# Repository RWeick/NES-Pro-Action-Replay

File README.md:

# NES-Pro-Action-Replay
Everything necessary to produce the Pro Action Replay for the NES. Happy making.

The PAL's logic decodes to:

/SRAM.CS1.OE = ROMSEL.Sys and Addr: 0x5000 - 0x5FFF

/CPU_FF_CLK = /ROMSEL.Sys and PPU_EN and Addr: 0x7FFA

/PPU_FF_CLK = /ROMSEL.Sys and Addr: 0x7FF8

PCB Thickness: 1.6 mm

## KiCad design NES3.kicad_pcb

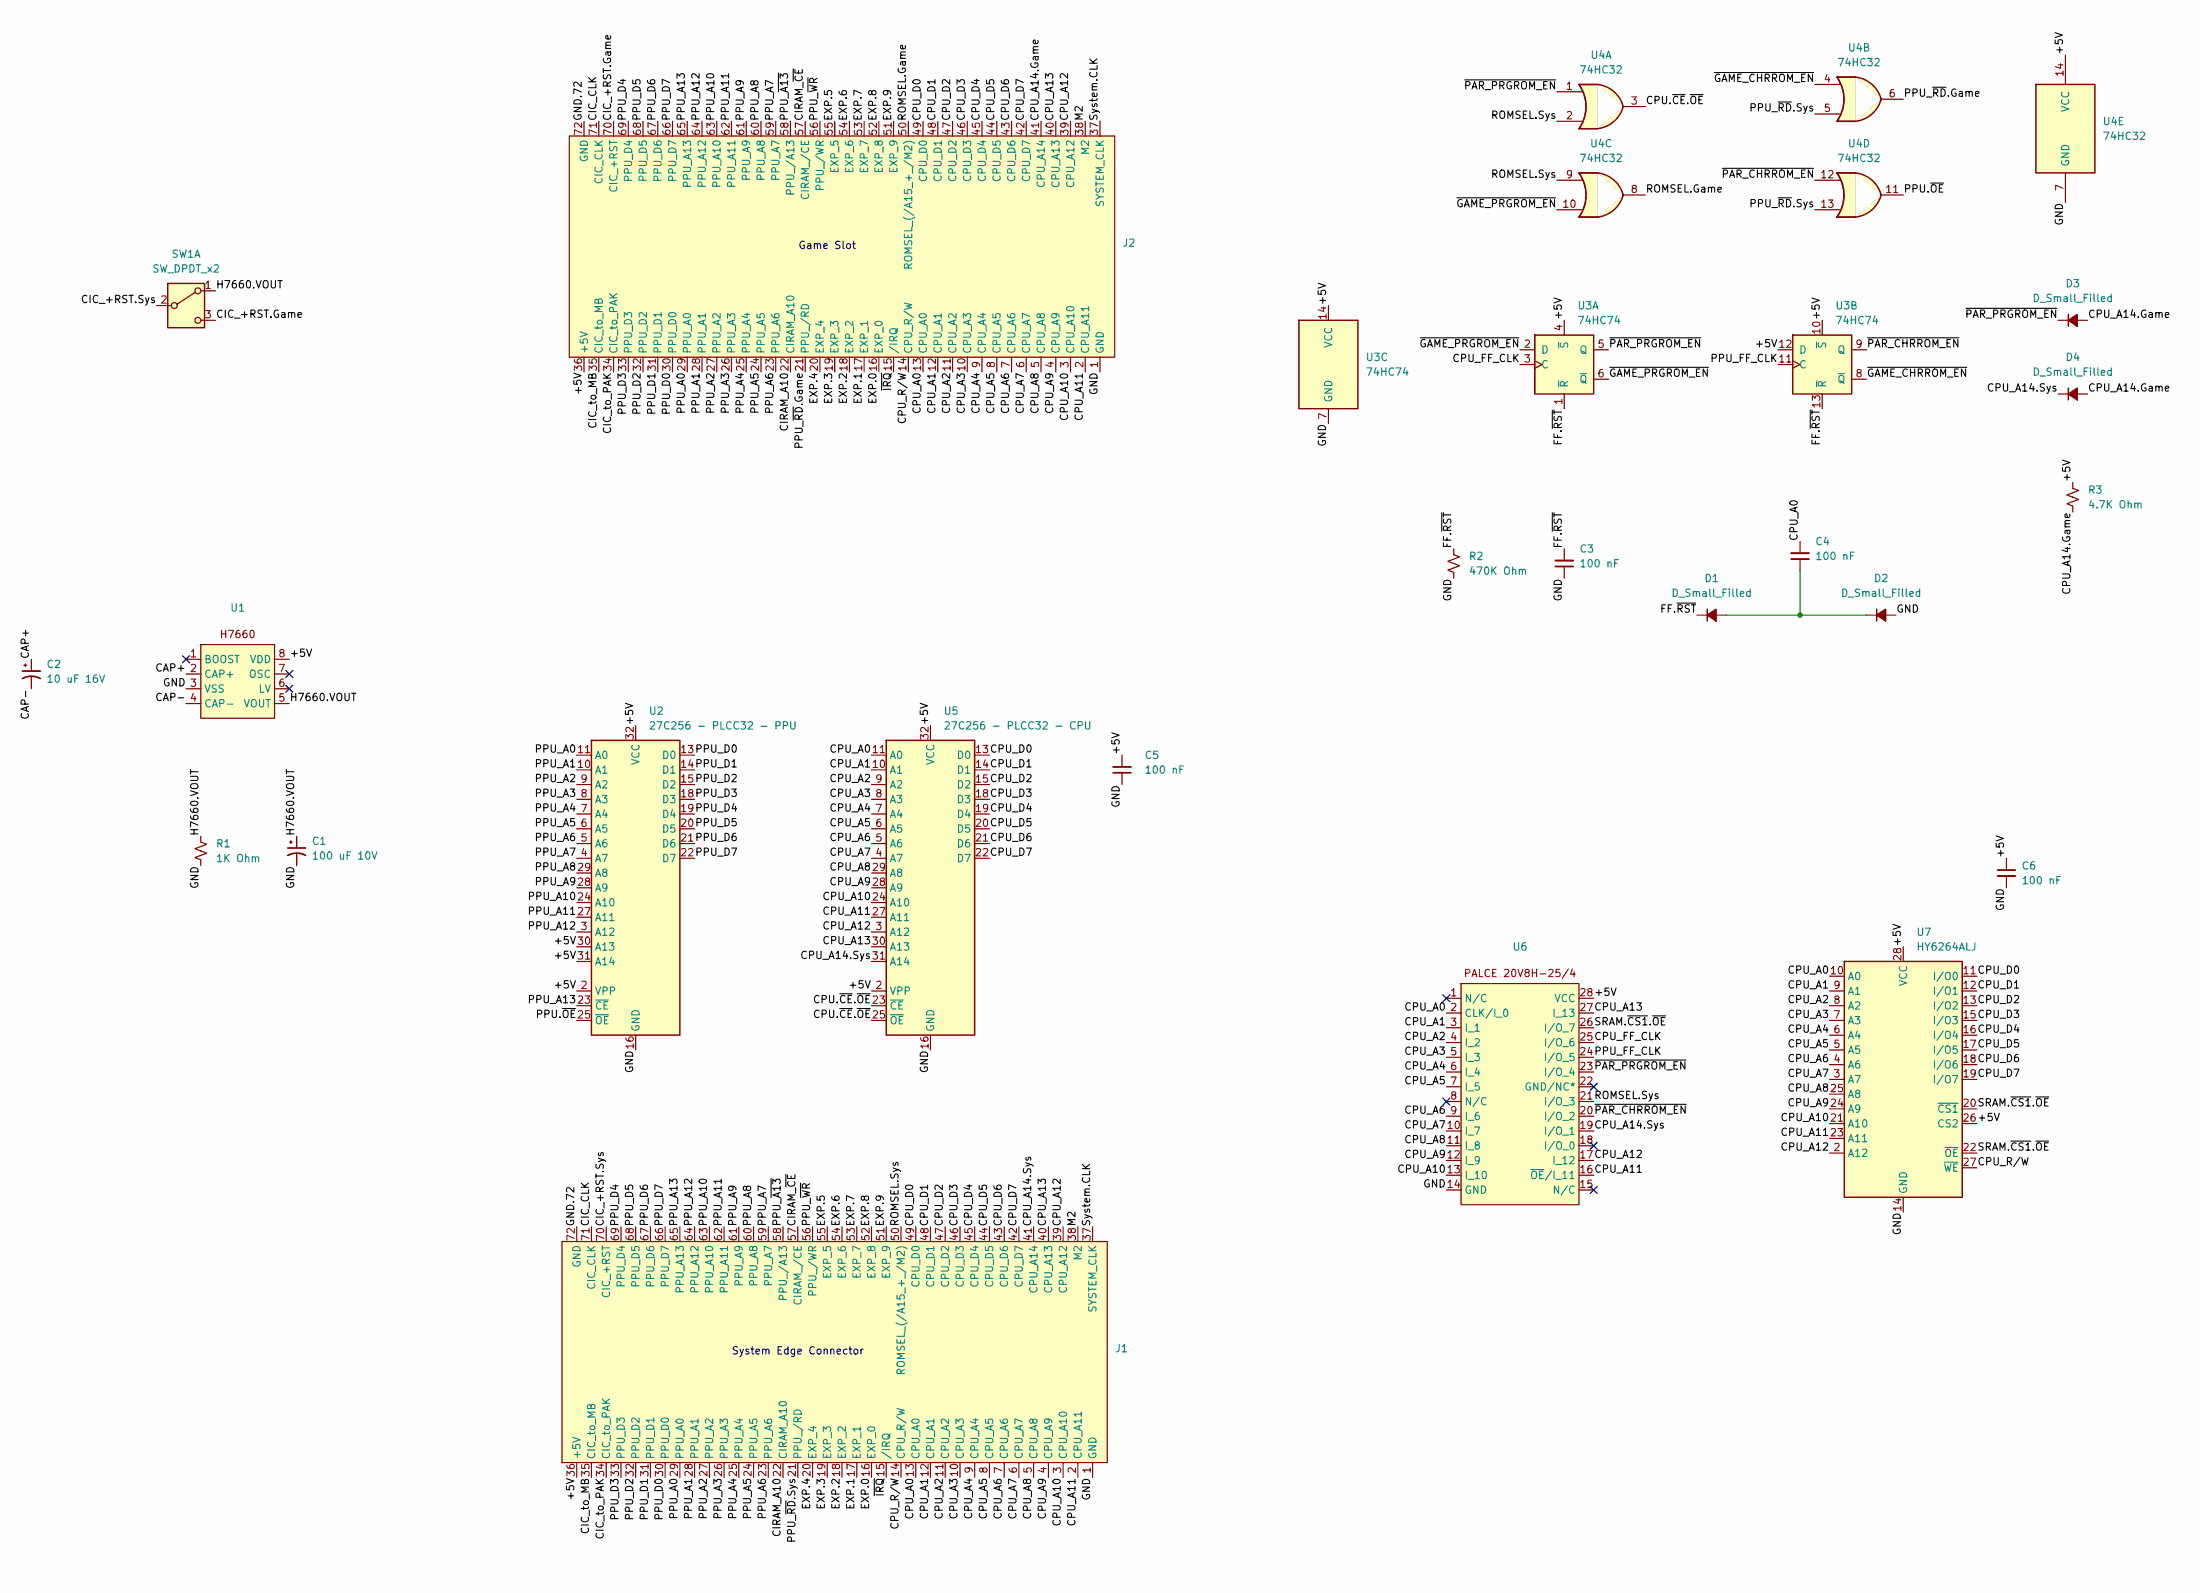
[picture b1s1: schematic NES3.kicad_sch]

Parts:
C1: 100 uF 10V; THT Caps
C2: 10 uF 16V; THT Caps
C3, C4, C5, C6: 100 nF; SMD Passive
D1, D2, D3, D4: D_Small_Filled; SMD Passive
J1: System Edge Connector
J2: Game Cartridge Slot
R1: 1K Ohm; SMD Passive
R2: 470K Ohm; SMD Passive
R3: 4.7K Ohm; SMD Passive
SW1: SW_DPDT_x2; Switch
U1: SOP-8
U2: 27C256 - PLCC32 - PPU; 27C256
U3: 74HC74; SOP-14
U4: 74HC32; SOP-14
U5: 27C256 - PLCC32 - CPU; 27C256
U6: PLCC-28
U7: HY6264ALJ; SRAM

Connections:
/+5V: C5.2, C6.1, J1.36 (+5V), J2.36 (+5V), R3.1, U1.8 (VDD), U2.2 (VPP), U2.30 (A13), U2.31 (A14), U2.32 (VCC), U3.4 (~S), U3.10 (~S), U3.12 (D), U3.14 (VCC), U4.14 (VCC), U5.2 (VPP), U5.32 (VCC), U6.28 (VCC), U7.26 (CS2), U7.28 (VCC)
/CAP+: C2.1, U1.2 (CAP+)
/CAP-: C2.2, U1.4 (CAP-)
/CIC_+RST.Game: J2.70 (CIC_+RST), SW1.3 (C)
/CIC_+RST.Sys: J1.70 (CIC_+RST), SW1.2 (B)
/CIC_CLK: J1.71 (CIC_CLK), J2.71 (CIC_CLK)
/CIC_to_MB: J1.35 (CIC_to_MB), J2.35 (CIC_to_MB)
/CIC_to_PAK: J1.34 (CIC_to_PAK), J2.34 (CIC_to_PAK)
/CIRAM_A10: J1.22 (CIRAM_A10), J2.22 (CIRAM_A10)
/CIRAM_~CE: J1.57 (CIRAM_/CE), J2.57 (CIRAM_/CE)
/CPU.~CE.~OE: U4.3, U5.23 (~CE), U5.25 (~OE)
/CPU_A0: C4.2, J1.13 (CPU_A0), J2.13 (CPU_A0), U5.11 (A0), U6.2 (CLK/I_0), U7.10 (A0)
/CPU_A1: J1.12 (CPU_A1), J2.12 (CPU_A1), U5.10 (A1), U6.3 (I_1), U7.9 (A1)
/CPU_A2: J1.11 (CPU_A2), J2.11 (CPU_A2), U5.9 (A2), U6.4 (I_2), U7.8 (A2)
/CPU_A3: J1.10 (CPU_A3), J2.10 (CPU_A3), U5.8 (A3), U6.5 (I_3), U7.7 (A3)
/CPU_A4: J1.9 (CPU_A4), J2.9 (CPU_A4), U5.7 (A4), U6.6 (I_4), U7.6 (A4)
/CPU_A5: J1.8 (CPU_A5), J2.8 (CPU_A5), U5.6 (A5), U6.7 (I_5), U7.5 (A5)
/CPU_A6: J1.7 (CPU_A6), J2.7 (CPU_A6), U5.5 (A6), U6.9 (I_6), U7.4 (A6)
/CPU_A7: J1.6 (CPU_A7), J2.6 (CPU_A7), U5.4 (A7), U6.10 (I_7), U7.3 (A7)
/CPU_A8: J1.5 (CPU_A8), J2.5 (CPU_A8), U5.29 (A8), U6.11 (I_8), U7.25 (A8)
/CPU_A9: J1.4 (CPU_A9), J2.4 (CPU_A9), U5.28 (A9), U6.12 (I_9), U7.24 (A9)
/CPU_A10: J1.3 (CPU_A10), J2.3 (CPU_A10), U5.24 (A10), U6.13 (I_10), U7.21 (A10)
/CPU_A11: J1.2 (CPU_A11), J2.2 (CPU_A11), U5.27 (A11), U6.16 (~OE/I_11), U7.23 (A11)
/CPU_A12: J1.39 (CPU_A12), J2.39 (CPU_A12), U5.3 (A12), U6.17 (I_12), U7.2 (A12)
/CPU_A13: J1.40 (CPU_A13), J2.40 (CPU_A13), U5.30 (A13), U6.27 (I_13)
/CPU_A14.Game: D3.2 (A), D4.2 (A), J2.41 (CPU_A14), R3.2
/CPU_A14.Sys: D4.1 (K), J1.41 (CPU_A14), U5.31 (A14), U6.19 (I/O_1)
/CPU_D0: J1.49 (CPU_D0), J2.49 (CPU_D0), U5.13 (D0), U7.11 (I/O0)
/CPU_D1: J1.48 (CPU_D1), J2.48 (CPU_D1), U5.14 (D1), U7.12 (I/O1)
/CPU_D2: J1.47 (CPU_D2), J2.47 (CPU_D2), U5.15 (D2), U7.13 (I/O2)
/CPU_D3: J1.46 (CPU_D3), J2.46 (CPU_D3), U5.18 (D3), U7.15 (I/O3)
/CPU_D4: J1.45 (CPU_D4), J2.45 (CPU_D4), U5.19 (D4), U7.16 (I/O4)
/CPU_D5: J1.44 (CPU_D5), J2.44 (CPU_D5), U5.20 (D5), U7.17 (I/O5)
/CPU_D6: J1.43 (CPU_D6), J2.43 (CPU_D6), U5.21 (D6), U7.18 (I/O6)
/CPU_D7: J1.42 (CPU_D7), J2.42 (CPU_D7), U5.22 (D7), U7.19 (I/O7)
/CPU_FF_CLK: U3.3 (C), U6.25 (I/O_6)
/CPU_R/W: J1.14 (CPU_R/W), J2.14 (CPU_R/W), U7.27 (~WE)
/EXP.0: J1.16 (EXP_0), J2.16 (EXP_0)
/EXP.1: J1.17 (EXP_1), J2.17 (EXP_1)
/EXP.2: J1.18 (EXP_2), J2.18 (EXP_2)
/EXP.3: J1.19 (EXP_3), J2.19 (EXP_3)
/EXP.4: J1.20 (EXP_4), J2.20 (EXP_4)
/EXP.5: J1.55 (EXP_5), J2.55 (EXP_5)
/EXP.6: J1.54 (EXP_6), J2.54 (EXP_6)
/EXP.7: J1.53 (EXP_7), J2.53 (EXP_7)
/EXP.8: J1.52 (EXP_8), J2.52 (EXP_8)
/EXP.9: J1.51 (EXP_9), J2.51 (EXP_9)
/FF.~RST: C3.2, D1.1 (K), R2.1, U3.1 (~R), U3.13 (~R)
/GND: C1.2, C3.1, C5.1, C6.2, D2.2 (A), J1.1 (GND), J2.1 (GND), R1.2, R2.2, U1.3 (VSS), U2.16 (GND), U3.7 (GND), U4.7 (GND), U5.16 (GND), U6.14 (GND), U7.14 (GND)
/GND.72: J1.72 (GND), J2.72 (GND)
/H7660.VOUT: C1.1, R1.1, SW1.1 (A), U1.5 (VOUT)
/M2: J1.38 (M2), J2.38 (M2)
/PPU.~OE: U2.25 (~OE), U4.11
/PPU_A0: J1.29 (PPU_A0), J2.29 (PPU_A0), U2.11 (A0)
/PPU_A1: J1.28 (PPU_A1), J2.28 (PPU_A1), U2.10 (A1)
/PPU_A2: J1.27 (PPU_A2), J2.27 (PPU_A2), U2.9 (A2)
/PPU_A3: J1.26 (PPU_A3), J2.26 (PPU_A3), U2.8 (A3)
/PPU_A4: J1.25 (PPU_A4), J2.25 (PPU_A4), U2.7 (A4)
/PPU_A5: J1.24 (PPU_A5), J2.24 (PPU_A5), U2.6 (A5)
/PPU_A6: J1.23 (PPU_A6), J2.23 (PPU_A6), U2.5 (A6)
/PPU_A7: J1.59 (PPU_A7), J2.59 (PPU_A7), U2.4 (A7)
/PPU_A8: J1.60 (PPU_A8), J2.60 (PPU_A8), U2.29 (A8)
/PPU_A9: J1.61 (PPU_A9), J2.61 (PPU_A9), U2.28 (A9)
/PPU_A10: J1.63 (PPU_A10), J2.63 (PPU_A10), U2.24 (A10)
/PPU_A11: J1.62 (PPU_A11), J2.62 (PPU_A11), U2.27 (A11)
/PPU_A12: J1.64 (PPU_A12), J2.64 (PPU_A12), U2.3 (A12)
/PPU_A13: J1.65 (PPU_A13), J2.65 (PPU_A13), U2.23 (~CE)
/PPU_D0: J1.30 (PPU_D0), J2.30 (PPU_D0), U2.13 (D0)
/PPU_D1: J1.31 (PPU_D1), J2.31 (PPU_D1), U2.14 (D1)
/PPU_D2: J1.32 (PPU_D2), J2.32 (PPU_D2), U2.15 (D2)
/PPU_D3: J1.33 (PPU_D3), J2.33 (PPU_D3), U2.18 (D3)
/PPU_D4: J1.69 (PPU_D4), J2.69 (PPU_D4), U2.19 (D4)
/PPU_D5: J1.68 (PPU_D5), J2.68 (PPU_D5), U2.20 (D5)
/PPU_D6: J1.67 (PPU_D6), J2.67 (PPU_D6), U2.21 (D6)
/PPU_D7: J1.66 (PPU_D7), J2.66 (PPU_D7), U2.22 (D7)
/PPU_FF_CLK: U3.11 (C), U6.24 (I/O_5)
/PPU_~A13: J1.58 (PPU_/A13), J2.58 (PPU_/A13)
/PPU_~RD.Game: J2.21 (PPU_/RD), U4.6
/PPU_~RD.Sys: J1.21 (PPU_/RD), U4.5, U4.13
/PPU_~WR: J1.56 (PPU_/WR), J2.56 (PPU_/WR)
/ROMSEL.Game: J2.50 (ROMSEL_(/A15_+_/M2)), U4.8
/ROMSEL.Sys: J1.50 (ROMSEL_(/A15_+_/M2)), U4.2, U4.9, U6.21 (I/O_3)
/SRAM.~CS1.~OE: U6.26 (I/O_7), U7.20 (~CS1), U7.22 (~OE)
/System.CLK: J1.37 (SYSTEM_CLK), J2.37 (SYSTEM_CLK)
/~GAME_CHRROM_EN: U3.8 (~Q), U4.4
/~GAME_PRGROM_EN: U3.2 (D), U3.6 (~Q), U4.10
/~IRQ: J1.15 (/IRQ), J2.15 (/IRQ)
/~PAR_CHRROM_EN: U3.9 (Q), U4.12, U6.20 (I/O_2)
/~PAR_PRGROM_EN: D3.1 (K), U3.5 (Q), U4.1, U6.23 (I/O_4)
unnamed: C4.1, D1.2 (A), D2.1 (K)

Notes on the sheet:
System Edge Connector
Game Slot

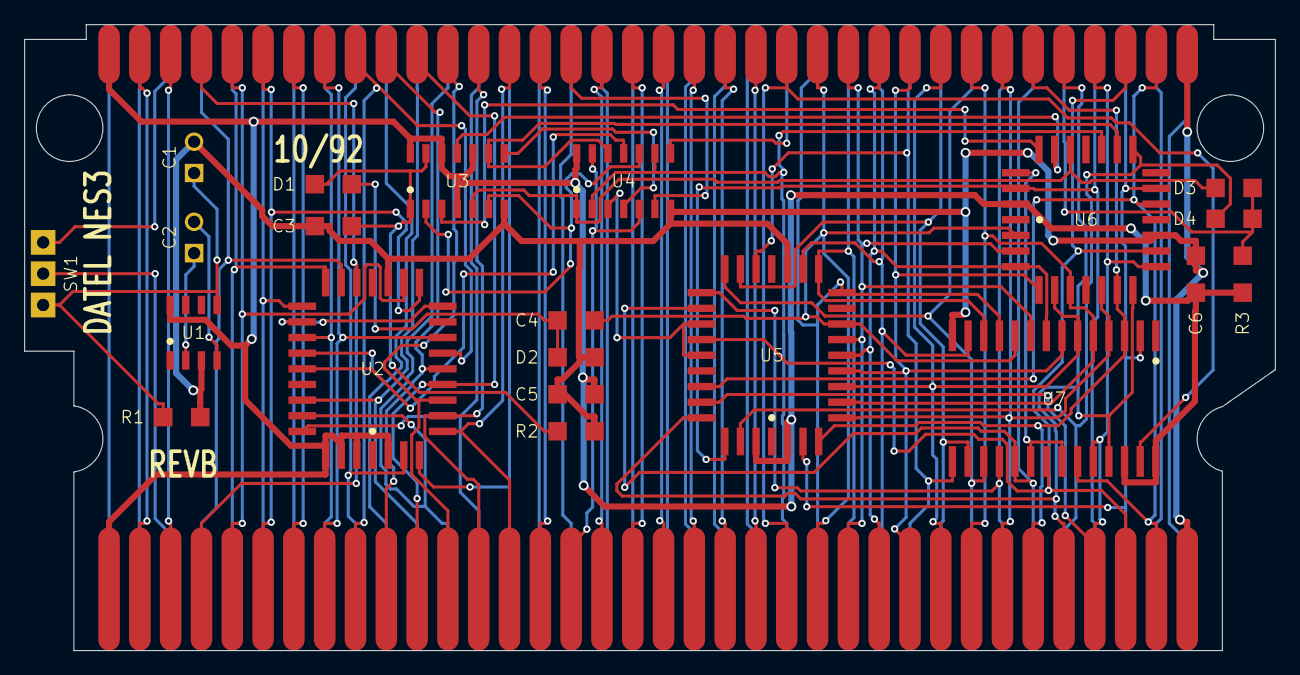
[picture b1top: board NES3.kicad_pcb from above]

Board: 2 copper layers, 101.5 x 50.8 mm, 23 parts (0 on the bottom side), 90 nets.
